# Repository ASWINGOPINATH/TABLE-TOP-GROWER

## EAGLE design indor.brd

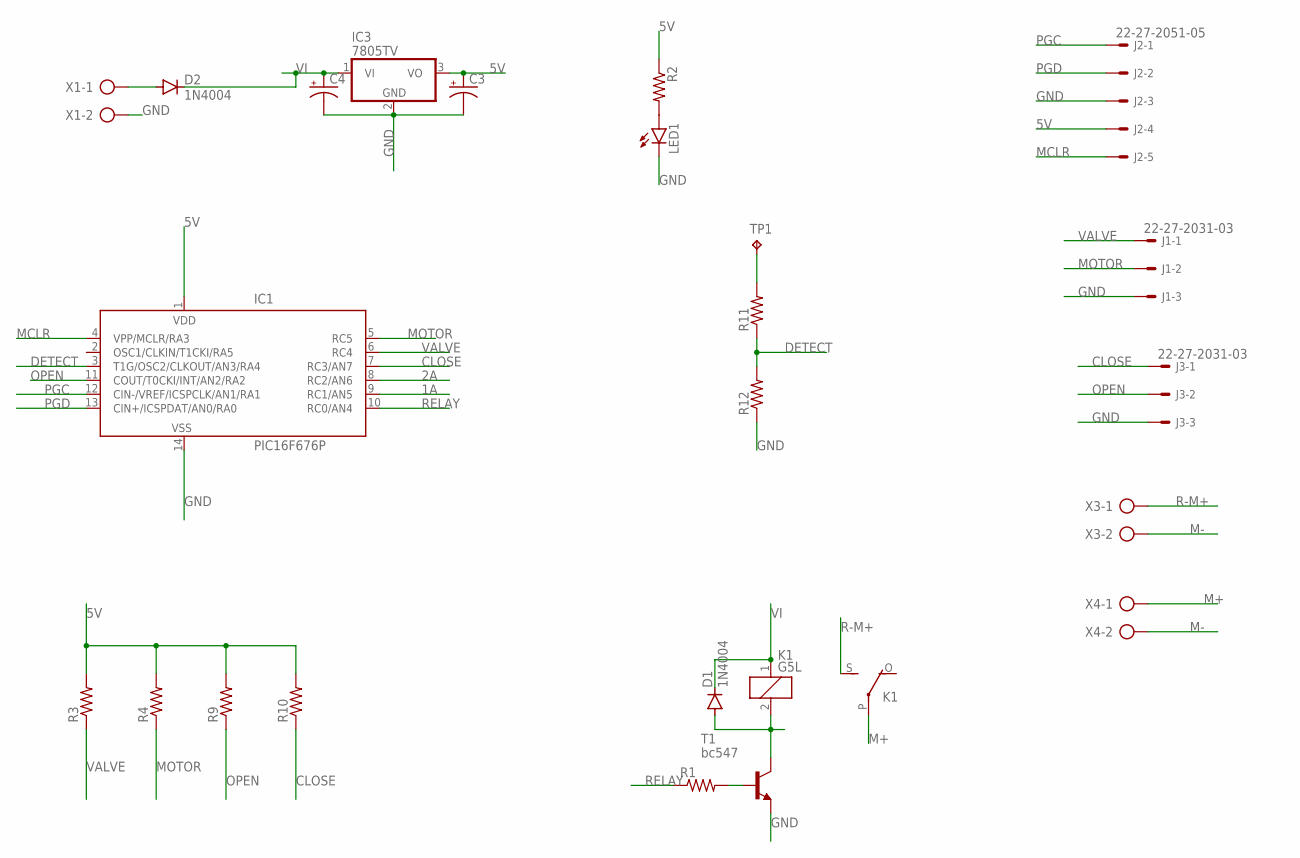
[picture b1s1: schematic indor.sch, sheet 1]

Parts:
C3, C4: CPOL-USE3.5-10; E3,5-10
D1, D2: 1N4004; DO41-10
IC1: PIC16F676P; DIL14
IC3: 7805TV; TO220V
J1, J3: 22-27-2031-03; 6410-03
J2: 22-27-2051-05; 6410-05
K1: G5L; G5LE
LED1: LED5MM
R1, R2, R3, R4, R9, R10, R11, R12: R-US_0207/10; 0207/10
T1: bc547; TO92-CBE
TP1: TPPAD1-13Y; P1-13Y
X1, X3, X4: AK500/2

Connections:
1A: IC1.9 (RC1/AN5); also elsewhere on the board
2A: IC1.8 (RC2/AN6); also elsewhere on the board
5V: C3.+, IC1.1 (VDD), IC3.3 (VO), J2.4, R2.1, R3.2, R4.2, R9.2, R10.2
CLOSE: IC1.7 (RC3/AN7), J3.1, R10.1
DETECT: IC1.3 (T1G/OSC2/CLKOUT/AN3/RA4), R11.1, R12.2
GND: C3.-, C4.-, IC1.14 (VSS), IC3.2 (GND), J1.3, J2.3, J3.3, LED1.K (C), R12.1, T1.E, X1.2; also elsewhere on the board
M+: K1.P, X4.1
M-: X3.2, X4.2
MCLR: IC1.4 (VPP/MCLR/RA3), J2.5
MOTOR: IC1.5 (RC5), J1.2, R4.1
unnamed: LED1.A, R2.2
unnamed: D2.A, X1.1
unnamed: R11.2, TP1.TP
unnamed: R1.2, T1.B
unnamed: D1.A, K1.2, T1.C
OPEN: IC1.11 (COUT/T0CKI/INT/AN2/RA2), J3.2, R9.1
PGC: IC1.12 (CIN-/VREF/ICSPCLK/AN1/RA1), J2.1
PGD: IC1.13 (CIN+/ICSPDAT/AN0/RA0), J2.2
R-M+: K1.S, X3.1
RELAY: IC1.10 (RC0/AN4), R1.1
VALVE: IC1.6 (RC4), J1.1, R3.1
VI: C4.+, D1.C, D2.C, IC3.1 (VI), K1.1; also elsewhere on the board

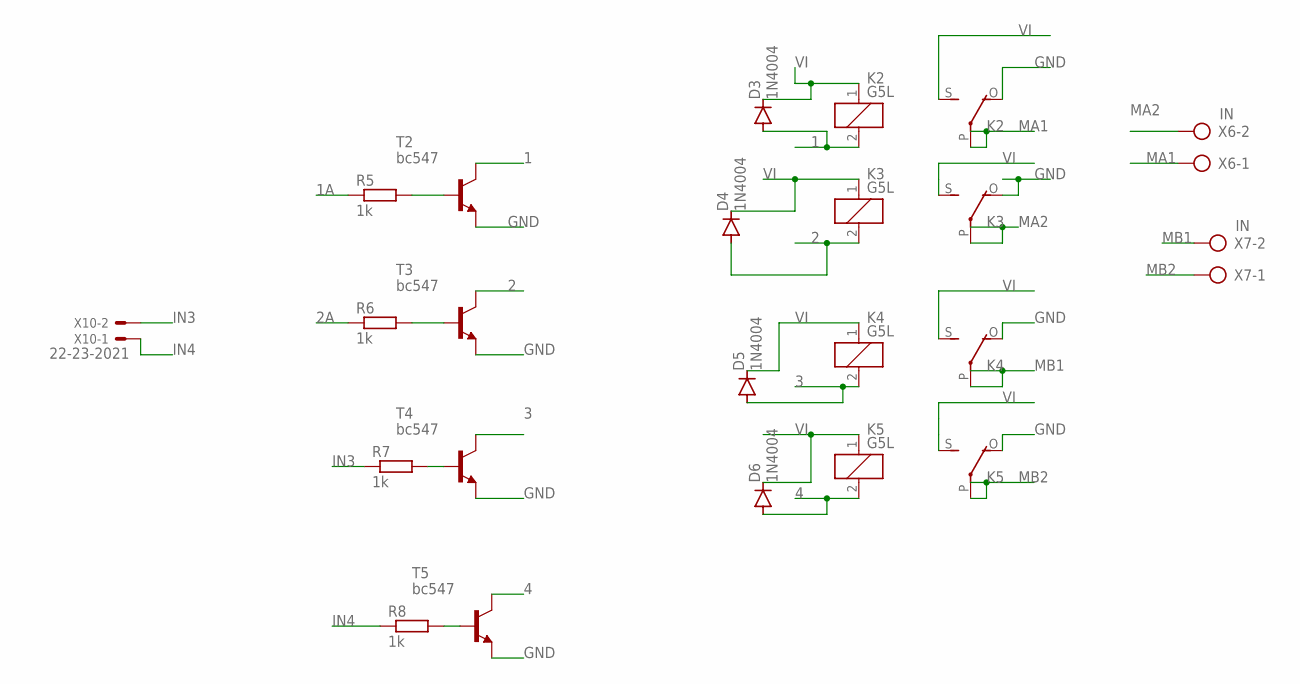
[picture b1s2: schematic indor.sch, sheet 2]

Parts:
D3, D4, D5, D6: 1N4004; DO41-10
K2, K3, K4, K5: G5L; G5LE
R5, R6, R7, R8: 1k; 0207/10
T2, T3, T4, T5: bc547; TO92-CBE
X6, X7: IN; AK500/2
X10: 22-23-2021

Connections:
1: D3.A, K2.2, T2.C
1A: R5.1; also elsewhere on the board
2: D4.A, K3.2, T3.C
2A: R6.1; also elsewhere on the board
3: D5.A, K4.2, T4.C
4: D6.A, K5.2, T5.C
GND: K2.O, K3.O, K4.O, K5.O, T2.E, T3.E, T4.E, T5.E; also elsewhere on the board
IN3: R7.1, X10.2
IN4: R8.1, X10.1
MA1: K2.P, X6.1
MA2: K3.P, X6.2
MB1: K4.P, X7.2
MB2: K5.P, X7.1
unnamed: R8.2, T5.B
unnamed: R7.2, T4.B
unnamed: R6.2, T3.B
unnamed: R5.2, T2.B
VI: D3.C, D4.C, D5.C, D6.C, K2.1, K2.S, K3.1, K3.S, K4.1, K4.S, K5.1, K5.S; also elsewhere on the board

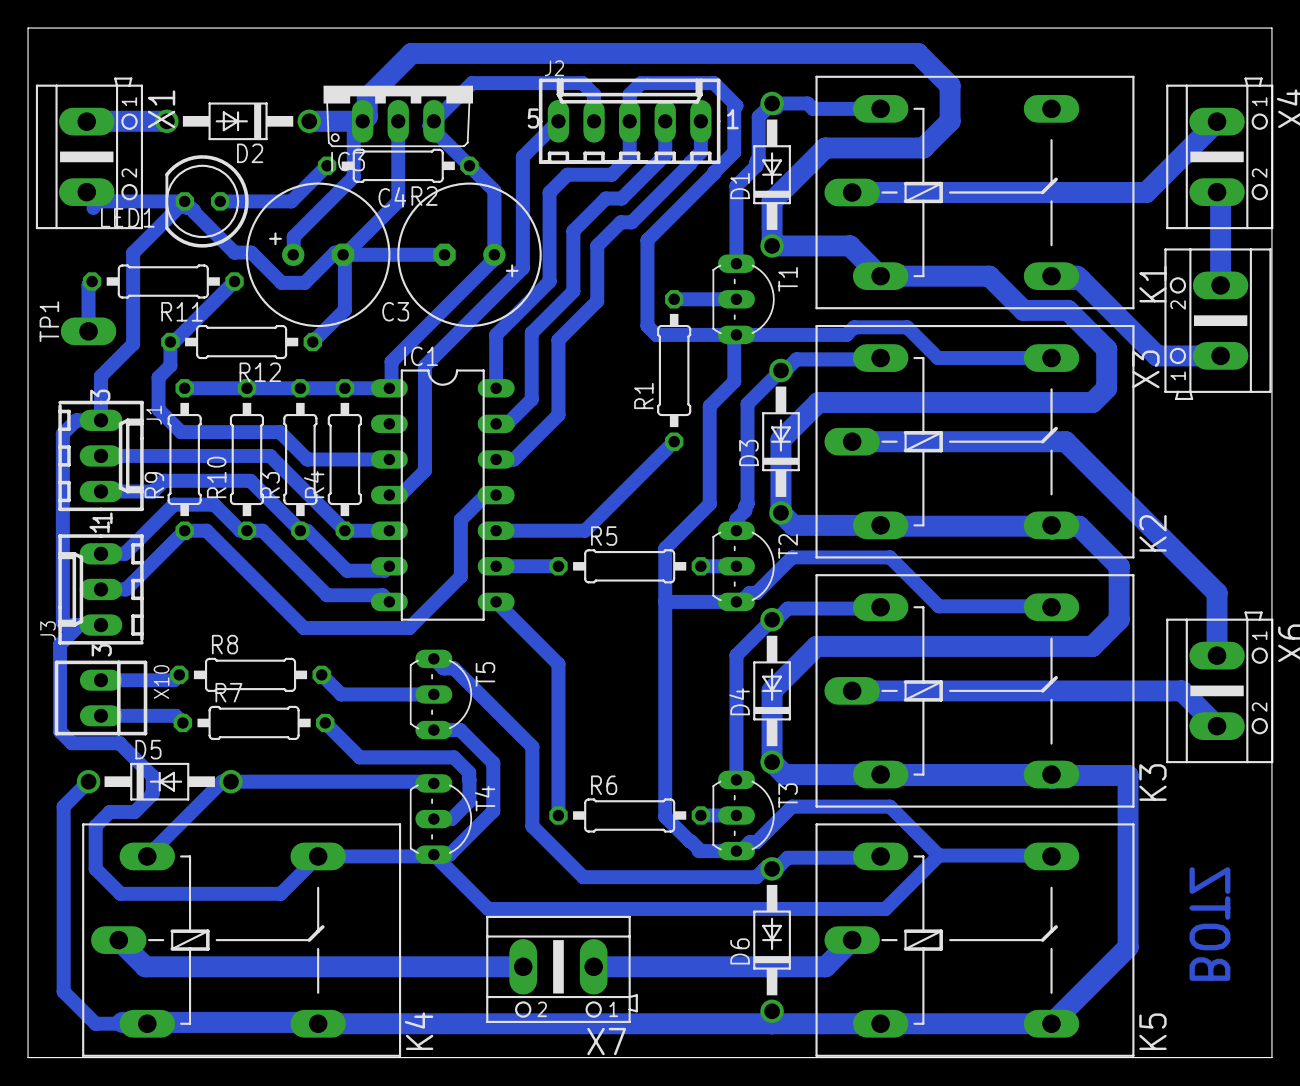
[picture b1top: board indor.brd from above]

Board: 2 copper layers, 88.8 x 73.5 mm, 43 parts (0 on the bottom side), 36 nets.

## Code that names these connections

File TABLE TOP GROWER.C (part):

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const int MotorB = 33;
const int MotorOn = 36;
const int MotorOff = 39;
const int Float_Valve = 14;  //when 0 valve will colse, when 1 valve will open
const int Float_Motor = 27;  //when 1 water pump will ON other wise Off
const int Valve_Open = 26;   // 0 when valve open
const int Valve_Close = 25;  // 0 when valve closed
const int Valve_M1 = 16;     //valve controlling motor pin
const int Valve_M2 = 17;     //valve controlling motor pin
const int Water_Motor = 18;   // water pump on of pin
long OnOffTime = 1500;
// NTP settings
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  // Set new times and angle
  html += "<div><h2>Set New Times and Angle:</h2>";
  html += "<form action='/setTimes' method='POST'>";
  html += "<label for='onTime1'>Valve On Time (HH:MM:SS):</label>";
  html += "<input type='time' id='onTime1' name='onTime1' step='1' value='" + formattedOnTime1 + "' required><br>";
  html += "<label for='offTime1'>Valve Off Time (HH:MM:SS):</label>";
  html += "<input type='time' id='offTime1' name='offTime1' step='1' value='" + formattedOffTime1 + "' required><br>";
  html += "<label for='onTime2'>Light On Time (HH:MM:SS):</label>";
  html += "<input type='time' id='onTime2' name='onTime2' step='1' value='" + formattedOnTime2 + "' required><br>";
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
